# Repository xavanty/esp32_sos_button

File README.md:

# ESP32 Botão de Emergência

Sistema de botão de pânico emergencial para idosos usando ESP32-C3 Super Mini com notificações via Telegram.

## Visão Geral

Este projeto implementa um sistema de botão de emergência com consumo ultra-baixo de energia que envia alertas instantâneos via Telegram quando acionado. O dispositivo permanece em modo deep sleep consumindo apenas ~10µA, tornando-o ideal para aplicações alimentadas por bateria.

## Funcionalidades

- **Consumo Ultra-Baixo de Energia**: ~10µA em modo deep sleep
- **Sistema de Dois Botões**:
  - GPIO2: Botão de Emergência/Pânico
  - GPIO3: Botão de Configuração
- **Integração com Telegram**:
  - Suporte a múltiplos destinatários (Chat IDs separados por vírgula)
  - Notificações com alarme sonoro
  - Múltiplas mensagens de alerta sequenciais
  - Funcionalidade de teste
- **Configuração via Web**:
  - Configuração de credenciais WiFi
  - Configuração do Token do Bot e Chat ID do Telegram
  - Ativação/desativação do alarme sonoro
  - Portal de configuração ao vivo
- **Portal Cativo**: Configuração automática na primeira inicialização ou quando a configuração está ausente
- **Armazenamento Persistente**: Configuração salva nas Preferences (NVS) do ESP32

## Requisitos de Hardware

- ESP32-C3 Super Mini
- 2x Botões de pressão (normalmente abertos)
- Bateria ou fonte de alimentação
- (Opcional) PCB personalizada - arquivos de projeto Eagle incluídos

## Configuração dos Pinos

| GPIO | Função | Conexão |
|------|--------|---------|
| GPIO2 | Botão de Emergência | Botão → GND |
| GPIO3 | Botão de Configuração | Botão → GND |

Ambos os pinos utilizam resistores pull-up internos e despertam o dispositivo com sinal LOW.

## Requisitos de Software

### Bibliotecas Arduino

Instale estas bibliotecas pelo Gerenciador de Bibliotecas do Arduino:

- `WiFi` (integrada)
- `HTTPClient` (integrada)
- `WiFiManager` por tzapu
- `Preferences` (integrada)
- `WebServer` (integrada)

### Configuração do Bot do Telegram

1. Abra o Telegram e procure por [@BotFather](https://t.me/BotFather)
2. Envie o comando `/newbot` e siga as instruções para criar seu bot
3. Ao final, o BotFather enviará o **API Token** do seu bot (formato: `123456789:ABCdefGHIjklMNO...`). **Copie e guarde este token**, pois ele será necessário na configuração do dispositivo
4. Obtenha seu Chat ID:
   - **Recomendado: Crie um grupo no Telegram** para receber as notificações de emergência
   - Adicione o seu bot ao grupo
   - Adicione ao grupo todas as pessoas que desejam receber as notificações de emergência (familiares, cuidadores, etc.)
   - Envie qualquer mensagem no grupo
   - Em seguida, acesse a seguinte URL no navegador, usando o token coletado no passo 3:
     ```
     https://api.telegram.org/bot<SEU_TOKEN_DO_PASSO_3>/getUpdates
     ```
   - No resultado JSON, procure pelo campo `"chat":{"id":` — esse número é o **Chat ID do grupo**
   - **Atenção**: o ID de grupo sempre começa com `-` (sinal de menos), por exemplo: `-1001234567890`. Inclua o `-` ao configurar o dispositivo

## Instalação

1. Clone este repositório:
   ```bash
   git clone https://github.com/yourusername/esp32_sos_button.git
   ```

2. Abra o arquivo `botao_emergencia_2_BOTOES.ino` na Arduino IDE

3. Selecione a placa: **ESP32C3 Dev Module**

4. Faça o upload do código para o seu ESP32-C3

## Configuração

### Primeira Configuração

1. Ligue o dispositivo — como ainda não há configuração de WiFi salva, ele entra automaticamente no modo de configuração
2. Conecte-se à rede WiFi: `BotaoEmergencia_Config` (senha: `12345678`)
3. Acesse o portal web pelo IP mostrado no Monitor Serial
4. Insira suas configurações:
   - SSID e Senha do WiFi
   - Token do Bot do Telegram
   - Chat ID(s) - múltiplos IDs separados por vírgula
   - Preferência de alarme sonoro

### Via Comandos Serial

Você também pode configurar pelo Monitor Serial (9600 baud):

- `CONFIG` - Entrar no modo de configuração
- `RESET` - Limpar todas as configurações salvas

## Uso

### Operação Normal

1. O dispositivo entra em deep sleep após a configuração
2. Pressione o **Botão de Emergência (GPIO2)** para acionar o alerta
3. O dispositivo acorda, conecta ao WiFi e envia:
   - Alarme sonoro (se habilitado)
   - 5 mensagens de aviso sequenciais
   - Alerta final detalhado com data e hora

### Sequência de Alerta

Quando o botão de emergência é pressionado:
```
🔊 Alarme sonoro (opcional)
🚨 ALERTA 1/5 - EMERGÊNCIA!
🚨 ALERTA 2/5 - EMERGÊNCIA!
🚨 ALERTA 3/5 - EMERGÊNCIA!
🚨 ALERTA 4/5 - EMERGÊNCIA!
🚨🚨🚨 EMERGÊNCIA ACIONADA! 🚨🚨🚨
⏰ [data e hora]
📍 Botão de pânico pressionado!
⚠️ VERIFIQUE IMEDIATAMENTE!
```

### Funcionalidades do Portal de Configuração

A interface web oferece:
- Exibição da configuração atual
- Configuração de credenciais WiFi
- Configuração do bot do Telegram
- Suporte a múltiplos destinatários
- Ativação/desativação do alarme sonoro
- Botão de teste para verificar a configuração
- Endpoint de status da configuração (`/status`)

## Projeto da PCB

O repositório inclui arquivos Eagle CAD para uma PCB personalizada:

- `placa.sch` - Esquemático
- `placa.brd` - Layout da placa
- `ESP32C3supermini.lbr` - Biblioteca personalizada do ESP32-C3 Super Mini

## Consumo de Energia

- Deep Sleep: ~10µA
- Ativo (WiFi): ~80-120mA (apenas por breves períodos)
- Estimativa de duração da bateria: Vários meses com uma única CR2032 (dependendo da frequência de uso)

## Solução de Problemas

### O dispositivo não conecta ao WiFi
- Mantenha pressionado o Botão de Configuração (GPIO3) ao ligar
- Conecte-se ao AP `BotaoEmergencia_Config`
- Reconfigure as definições de WiFi

### Telegram não está recebendo mensagens
- Verifique se o Token do Bot está correto
- Certifique-se de que o Chat ID é válido
- Verifique se o bot tem permissão para enviar mensagens ao usuário/grupo
- Use o botão de Teste no portal de configuração

### Restaurar para configurações de fábrica
- Envie o comando `RESET` pelo Monitor Serial (9600 baud)
- Ou mantenha o Botão de Configuração pressionado e envie `RESET`

## Licença

Este projeto está licenciado sob a Licença Pública Geral GNU v3.0 - veja o arquivo [LICENSE](LICENSE) para detalhes.

## Contribuições

Contribuições são bem-vindas! Sinta-se à vontade para enviar um Pull Request.

## Aviso de Segurança

Este dispositivo é destinado como uma medida de segurança adicional e não deve ser o único sistema de emergência. Sempre garanta que métodos adequados de contato com serviços de emergência estejam disponíveis.

## Autor

Criado para aplicações de cuidado de idosos e resposta a emergências.

## Agradecimentos

- Construído na plataforma ESP32-C3
- Utiliza a biblioteca WiFiManager para configuração fácil
- API de Bot do Telegram para notificações

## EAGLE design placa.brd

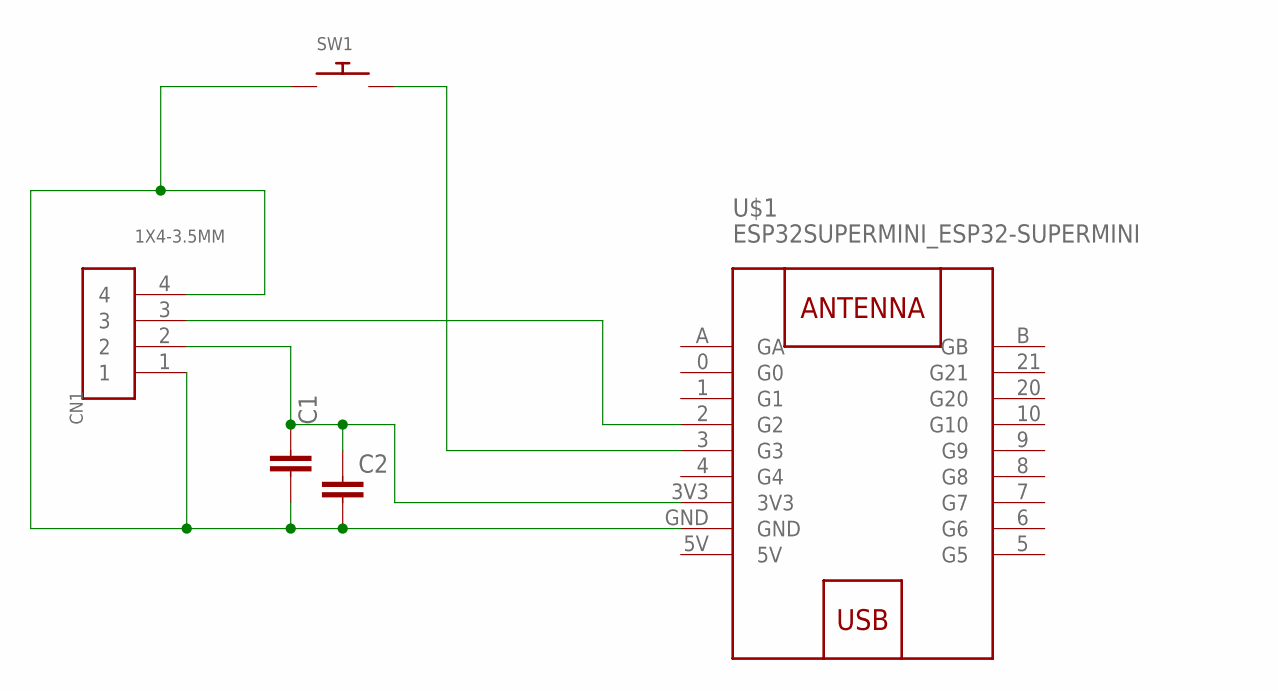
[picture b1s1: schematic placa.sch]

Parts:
C2: C-EU025-024X044; C025-024X044
CN1: 1X4-3.5MM; 1X04-3.5MM
SW1: SWITCH_PUSHBUTTONEVQ-PE; TACT_PANA-EVQ
U$1: ESP32SUPERMINI_ESP32-SUPERMINI

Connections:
5V: U$1.5V
unnamed: C2.2, CN1.1, CN1.4, SW1.P$1, U$1.GND
unnamed: C2.1, CN1.2, U$1.3V3
unnamed: CN1.3, U$1.2 (G2)
unnamed: SW1.P$2, U$1.3 (G3)

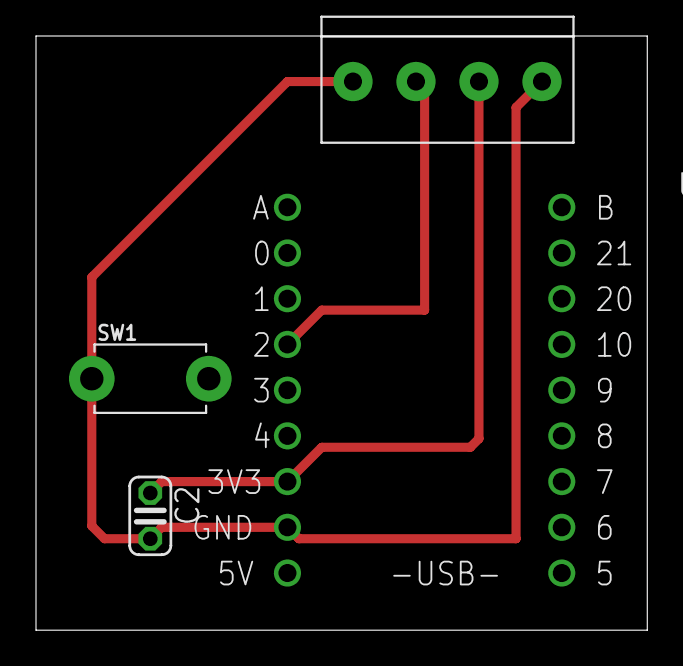
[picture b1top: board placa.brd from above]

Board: 2 copper layers, 34.0 x 33.0 mm, 4 parts (0 on the bottom side), 4 nets.

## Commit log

2026-02-08 Arquivo inicial do projeto
2026-02-08 arquivos
2026-02-08 atualização do README com instruções
